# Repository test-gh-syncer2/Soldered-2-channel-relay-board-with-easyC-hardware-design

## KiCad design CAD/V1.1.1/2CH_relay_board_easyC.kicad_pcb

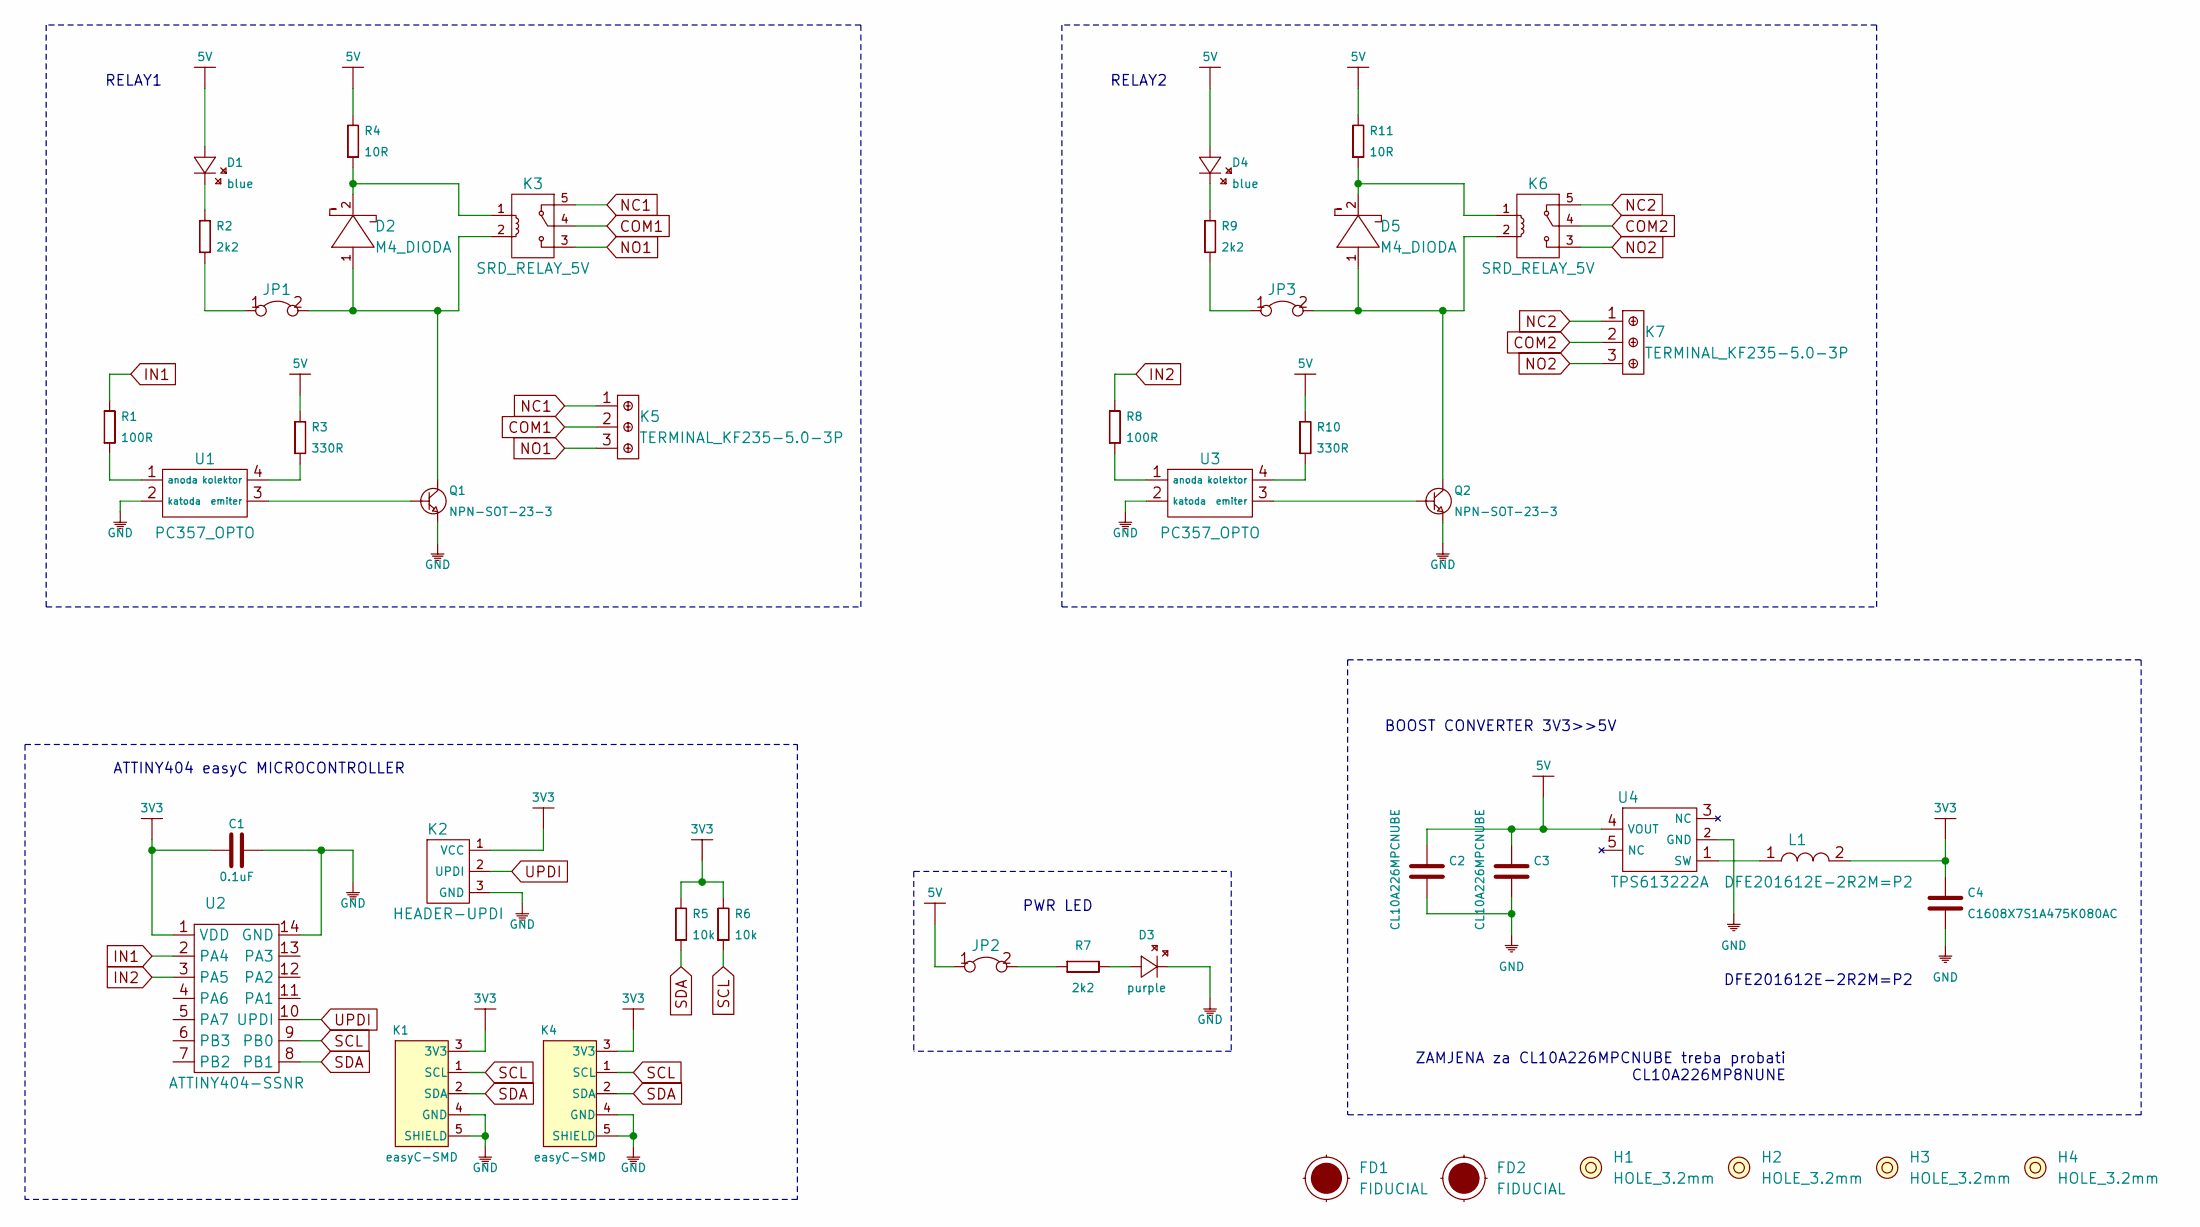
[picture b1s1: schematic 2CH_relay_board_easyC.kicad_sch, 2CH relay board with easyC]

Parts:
C1: 0.1uF; 0603C
C2, C3: CL10A226MPCNUBE; 0603C
C4: C1608X7S1A475K080AC; 0603C
D1, D4: blue; 0402LED
D2, D5: M4_DIODA
D3: purple; 0402LED
FD1, FD2: FIDUCIAL; FIDUCIAL_23
H1, H2, H3, H4: HOLE_3.2mm
JP1, JP2, JP3: SMD-JUMPER-CONNECTED_TRACE_SLODERMASK
K1, K4: easyC-SMD; easyC-connector
K2: HEADER-UPDI
K3, K6: SRD_RELAY_5V
K5, K7: TERMINAL_KF235-5.0-3P
L1: DFE201612E-2R2M=P2; 0806L
Q1, Q2: NPN-SOT-23-3; SOT-23-3
R1, R8: 100R; 0603R
R2, R7, R9: 2k2; 0402R
R3, R10: 330R; 0603R
R4, R11: 10R; 0603R
R5, R6: 10k; 0603R
U1, U3: PC357_OPTO
U2: ATTINY404-SSNR; SOIC-14
U4: TPS613222A; tps613222a

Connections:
3V3: C1.1, C4.2, K1.3 (3V3), K2.1 (VCC), K4.3 (3V3), L1.2, R5.2, R6.2, U2.1 (VDD)
5V: C2.2, C3.2, D1.1 (A), D4.1 (A), JP2.1, R3.2, R4.2, R10.2, R11.2, U4.4 (VOUT)
COM1: K3.4, K5.2
COM2: K6.4, K7.2
GND: C1.2, C2.1, C3.1, C4.1, D3.2 (K), K1.4 (GND), K1.5 (SHIELD), K2.3 (GND), K4.4 (GND), K4.5 (SHIELD), Q1.2 (E), Q2.2 (E), U1.2 (katoda), U2.14 (GND), U3.2 (katoda), U4.2 (GND)
IN1: R1.2, U2.2 (PA4)
IN2: R8.2, U2.3 (PA5)
NC1: K3.5, K5.1
NC2: K6.5, K7.1
NO1: K3.3, K5.3
NO2: K6.3, K7.3
unnamed: D1.2 (K), R2.2
unnamed: D2.1 (A), JP1.2, K3.2, Q1.3 (C)
unnamed: D2.2 (K), K3.1, R4.1
unnamed: D3.1 (A), R7.2
unnamed: D4.2 (K), R9.2
unnamed: D5.1 (A), JP3.2, K6.2, Q2.3 (C)
unnamed: D5.2 (K), K6.1, R11.1
unnamed: JP1.1, R2.1
unnamed: JP2.2, R7.1
unnamed: JP3.1, R9.1
unnamed: L1.1, U4.1 (SW)
unnamed: Q1.1 (B), U1.3 (emiter)
unnamed: Q2.1 (B), U3.3 (emiter)
unnamed: R1.1, U1.1 (anoda)
unnamed: R3.1, U1.4 (kolektor)
unnamed: R8.1, U3.1 (anoda)
unnamed: R10.1, U3.4 (kolektor)
SCL: K1.1 (SCL), K4.1 (SCL), R6.1, U2.9 (PB0)
SDA: K1.2 (SDA), K4.2 (SDA), R5.1, U2.8 (PB1)
UPDI: K2.2 (UPDI), U2.10 (UPDI)

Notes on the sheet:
RELAY1
ATTINY404 easyC MICROCONTROLLER
PWR LED
RELAY2
BOOST CONVERTER 3V3>>5V
ZAMJENA za CL10A226MPCNUBE treba probati CL10A226MP8NUNE
DFE201612E-2R2M=P2

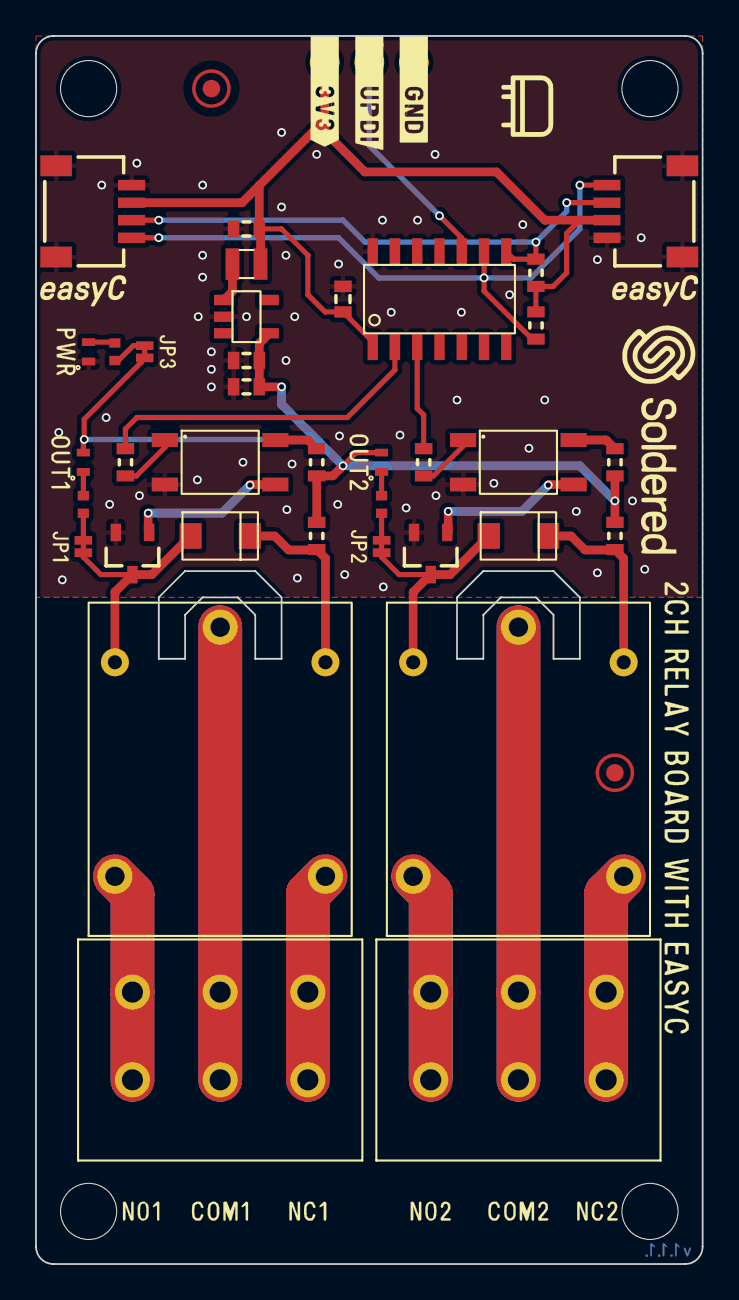
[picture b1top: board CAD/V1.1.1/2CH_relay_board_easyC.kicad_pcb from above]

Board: 2 copper layers, 38.0 x 70.0 mm, 43 parts (0 on the bottom side), 31 nets.

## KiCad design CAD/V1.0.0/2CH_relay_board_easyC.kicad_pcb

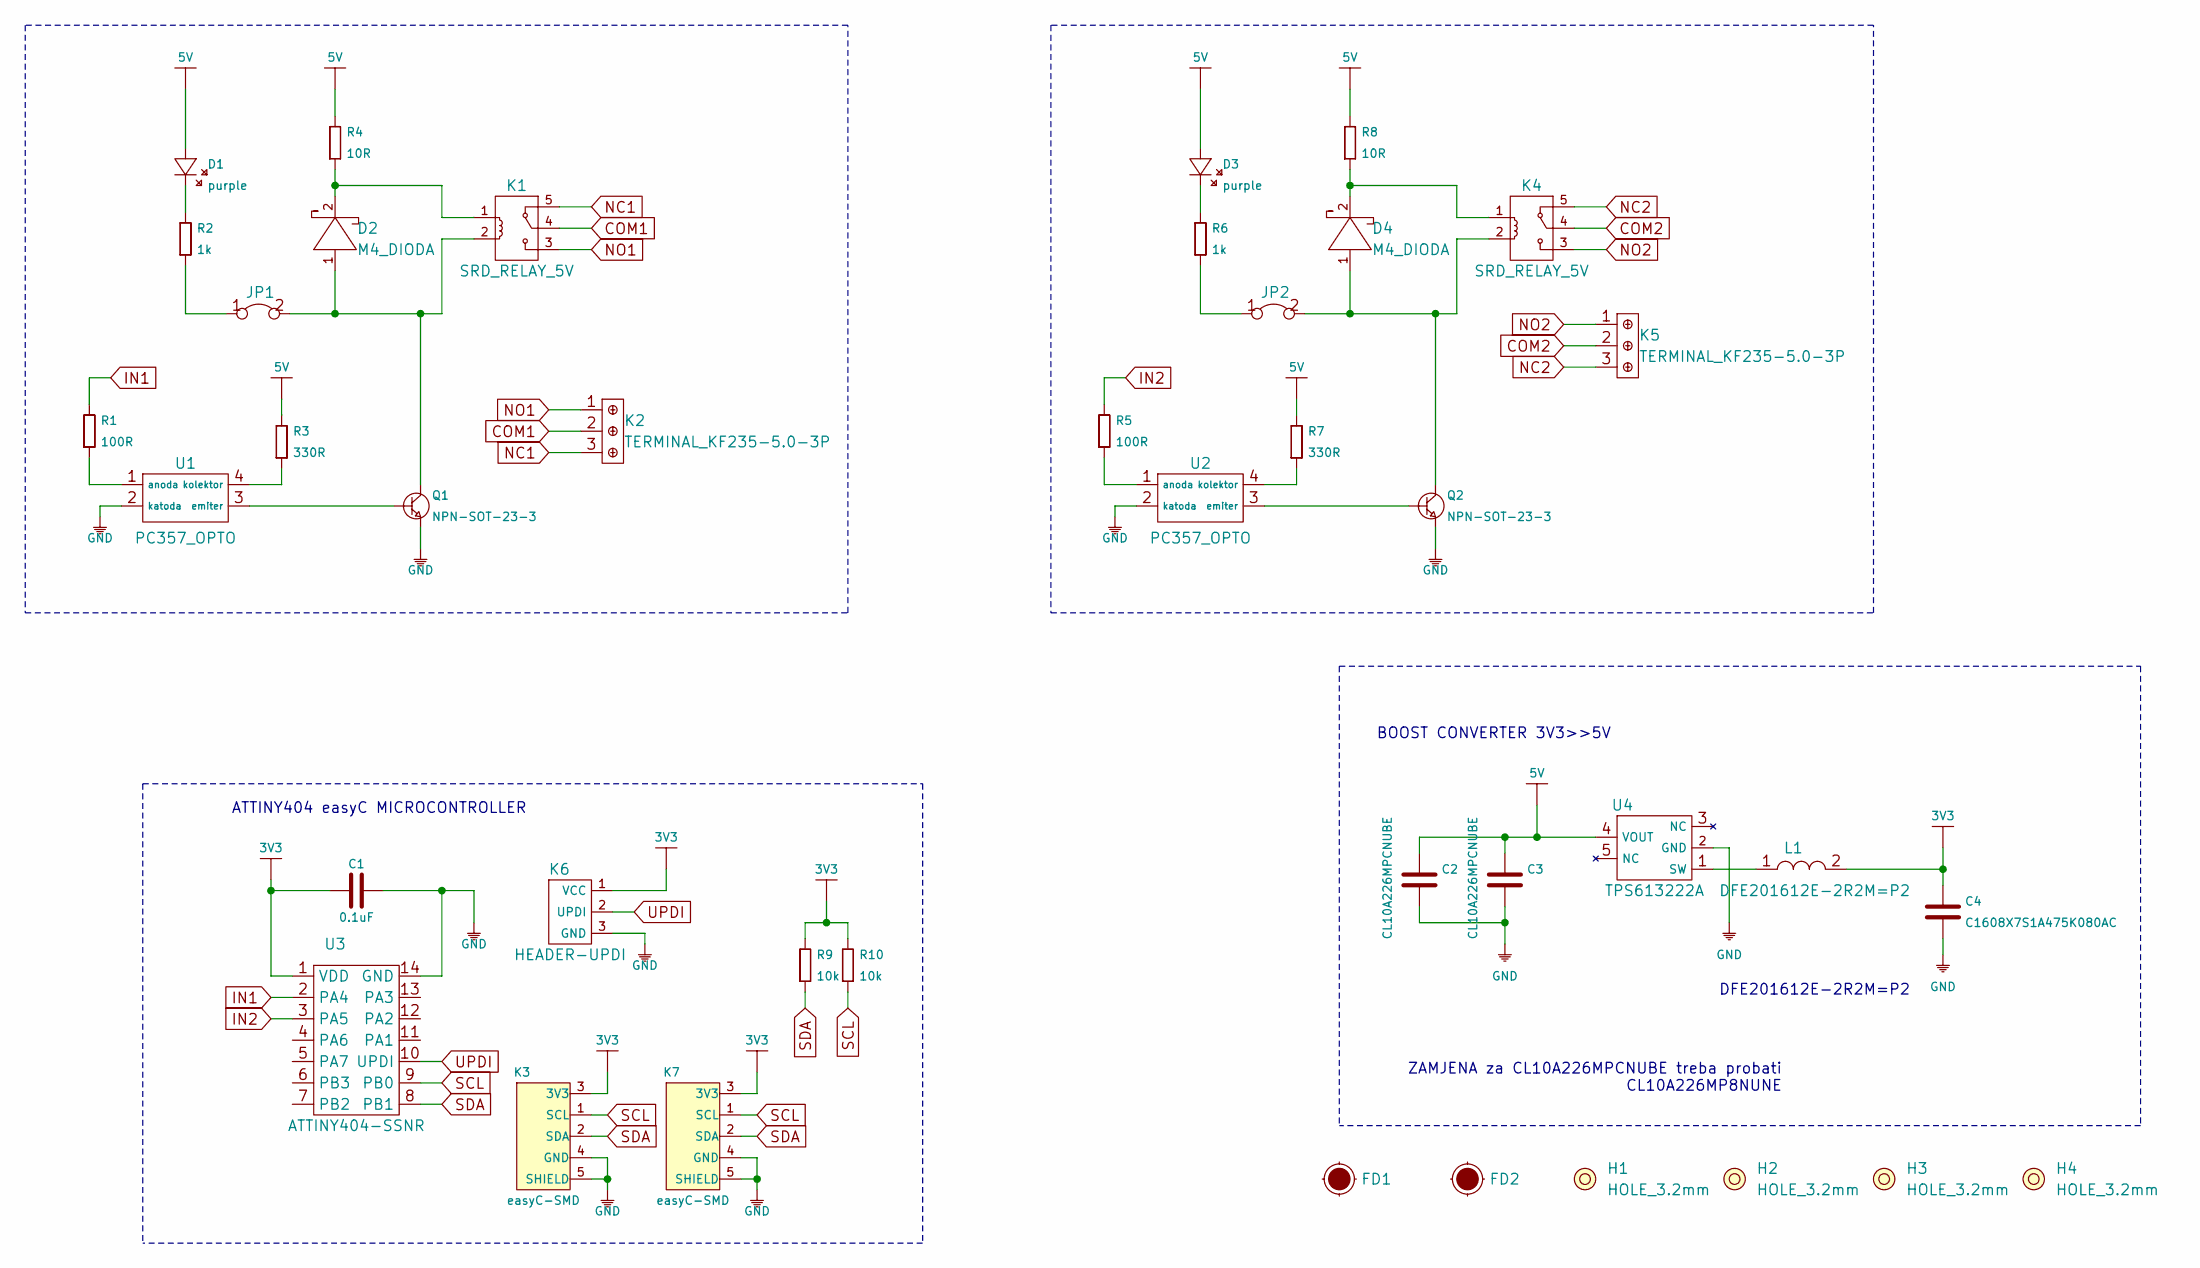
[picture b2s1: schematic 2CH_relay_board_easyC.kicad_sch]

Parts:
C1: 0.1uF; 0603C
C2, C3: CL10A226MPCNUBE; 0603C
C4: C1608X7S1A475K080AC; 0603C
D1, D3: purple; 0402LED
D2, D4: M4_DIODA
FD1, FD2: Fiducial_Stencil; FIDUCIAL_1MM_PASTE
H1, H2, H3, H4: HOLE_3.2mm
JP1, JP2: SMD-JUMPER-CONNECTED_TRACE_NOSLODERMASK
K1, K4: SRD_RELAY_5V
K2, K5: TERMINAL_KF235-5.0-3P
K3, K7: easyC-SMD; easyC-connector
K6: HEADER-UPDI
L1: DFE201612E-2R2M=P2; 0806L
Q1, Q2: NPN-SOT-23-3; SOT-23-3
R1, R5: 100R; 0603R
R2, R6: 1k; 0402R
R3, R7: 330R; 0603R
R4, R8: 10R; 0603R
R9, R10: 10k; 0603R
U1, U2: PC357_OPTO
U3: ATTINY404-SSNR; SOIC-14
U4: TPS613222A; tps613222a

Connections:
3V3: C1.1, C4.2, K3.3 (3V3), K6.1 (VCC), K7.3 (3V3), L1.2, R9.2, R10.2, U3.1 (VDD)
5V: C2.2, C3.2, D1.1 (A), D3.1 (A), R3.2, R4.2, R7.2, R8.2, U4.4 (VOUT)
COM1: K1.4, K2.2
COM2: K4.4, K5.2
GND: C1.2, C2.1, C3.1, C4.1, K3.4 (GND), K3.5 (SHIELD), K6.3 (GND), K7.4 (GND), K7.5 (SHIELD), Q1.2 (E), Q2.2 (E), U1.2 (katoda), U2.2 (katoda), U3.14 (GND), U4.2 (GND)
IN1: R1.2, U3.2 (PA4)
IN2: R5.2, U3.3 (PA5)
NC1: K1.5, K2.3
NC2: K4.5, K5.3
NO1: K1.3, K2.1
NO2: K4.3, K5.1
unnamed: D1.2 (K), R2.2
unnamed: D2.1 (A), JP1.2, K1.2, Q1.3 (C)
unnamed: D2.2 (K), K1.1, R4.1
unnamed: D3.2 (K), R6.2
unnamed: D4.1 (A), JP2.2, K4.2, Q2.3 (C)
unnamed: D4.2 (K), K4.1, R8.1
unnamed: JP1.1, R2.1
unnamed: JP2.1, R6.1
unnamed: L1.1, U4.1 (SW)
unnamed: Q1.1 (B), U1.3 (emiter)
unnamed: Q2.1 (B), U2.3 (emiter)
unnamed: R1.1, U1.1 (anoda)
unnamed: R3.1, U1.4 (kolektor)
unnamed: R5.1, U2.1 (anoda)
unnamed: R7.1, U2.4 (kolektor)
SCL: K3.1 (SCL), K7.1 (SCL), R10.1, U3.9 (PB0)
SDA: K3.2 (SDA), K7.2 (SDA), R9.1, U3.8 (PB1)
UPDI: K6.2 (UPDI), U3.10 (UPDI)

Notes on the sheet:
ATTINY404 easyC MICROCONTROLLER
BOOST CONVERTER 3V3>>5V
ZAMJENA za CL10A226MPCNUBE treba probati CL10A226MP8NUNE
DFE201612E-2R2M=P2

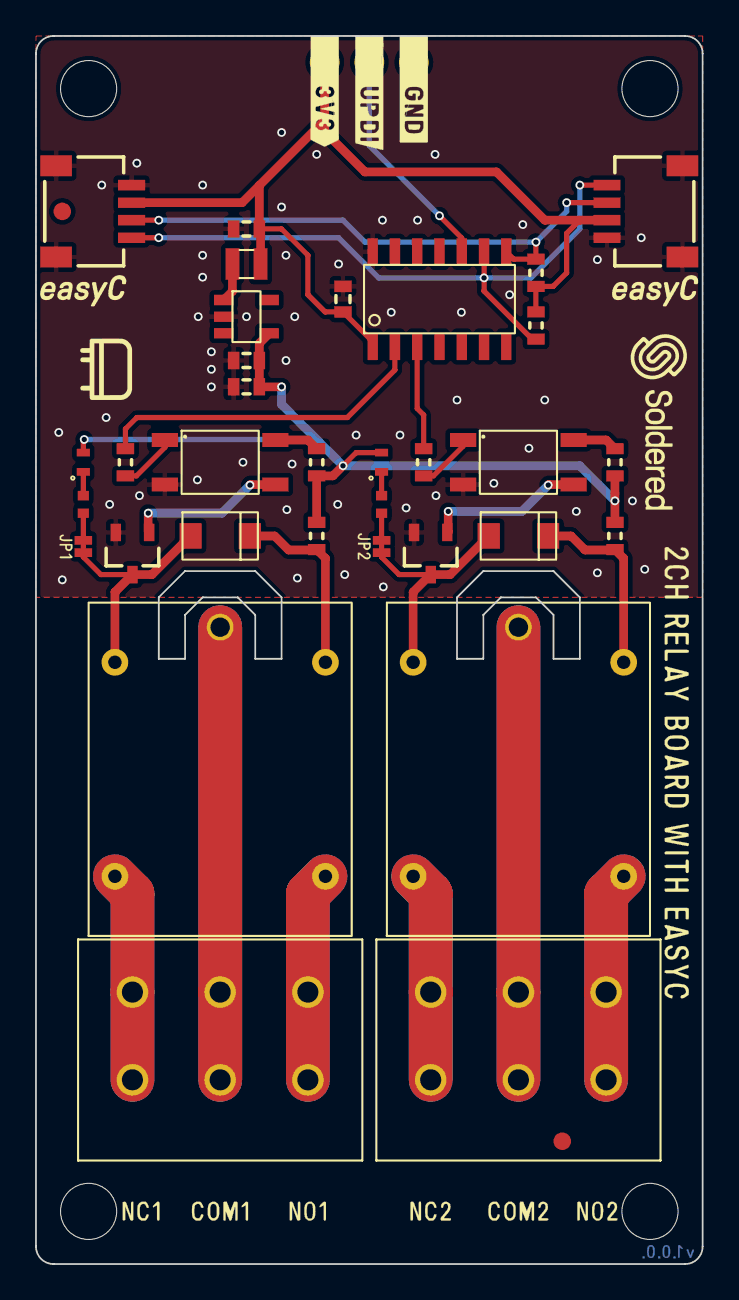
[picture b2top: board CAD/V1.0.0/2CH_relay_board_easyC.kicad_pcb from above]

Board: 2 copper layers, 38.0 x 70.0 mm, 40 parts (0 on the bottom side), 29 nets.

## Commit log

2021-09-23 Syncing to git
2021-09-23 Updating open source files.
